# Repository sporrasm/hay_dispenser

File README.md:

Readme for project horse_feeder

Remeber to run the export script from ESP install dir!

To configure (once per project), run

```
idf.py set-target esp32
idf.py menuconfig
```
Alternatively, WiFi SSID and password can be
set with `wifi_config.sh`. Place SSID and password
in `wifi_info.txt` in the following format:

```
SSID=YOUR_NETWORK_SSID
PASS=YOUR_PASSWORD
```
`wifi_info.txt` is automatically ignored in version
control and thus your password is safe.

To build, run
```
idf.py build
```
Finally, to flash and monitor, run

```
idf.py -p ESP_SERIAL_PORT flash monitor
```

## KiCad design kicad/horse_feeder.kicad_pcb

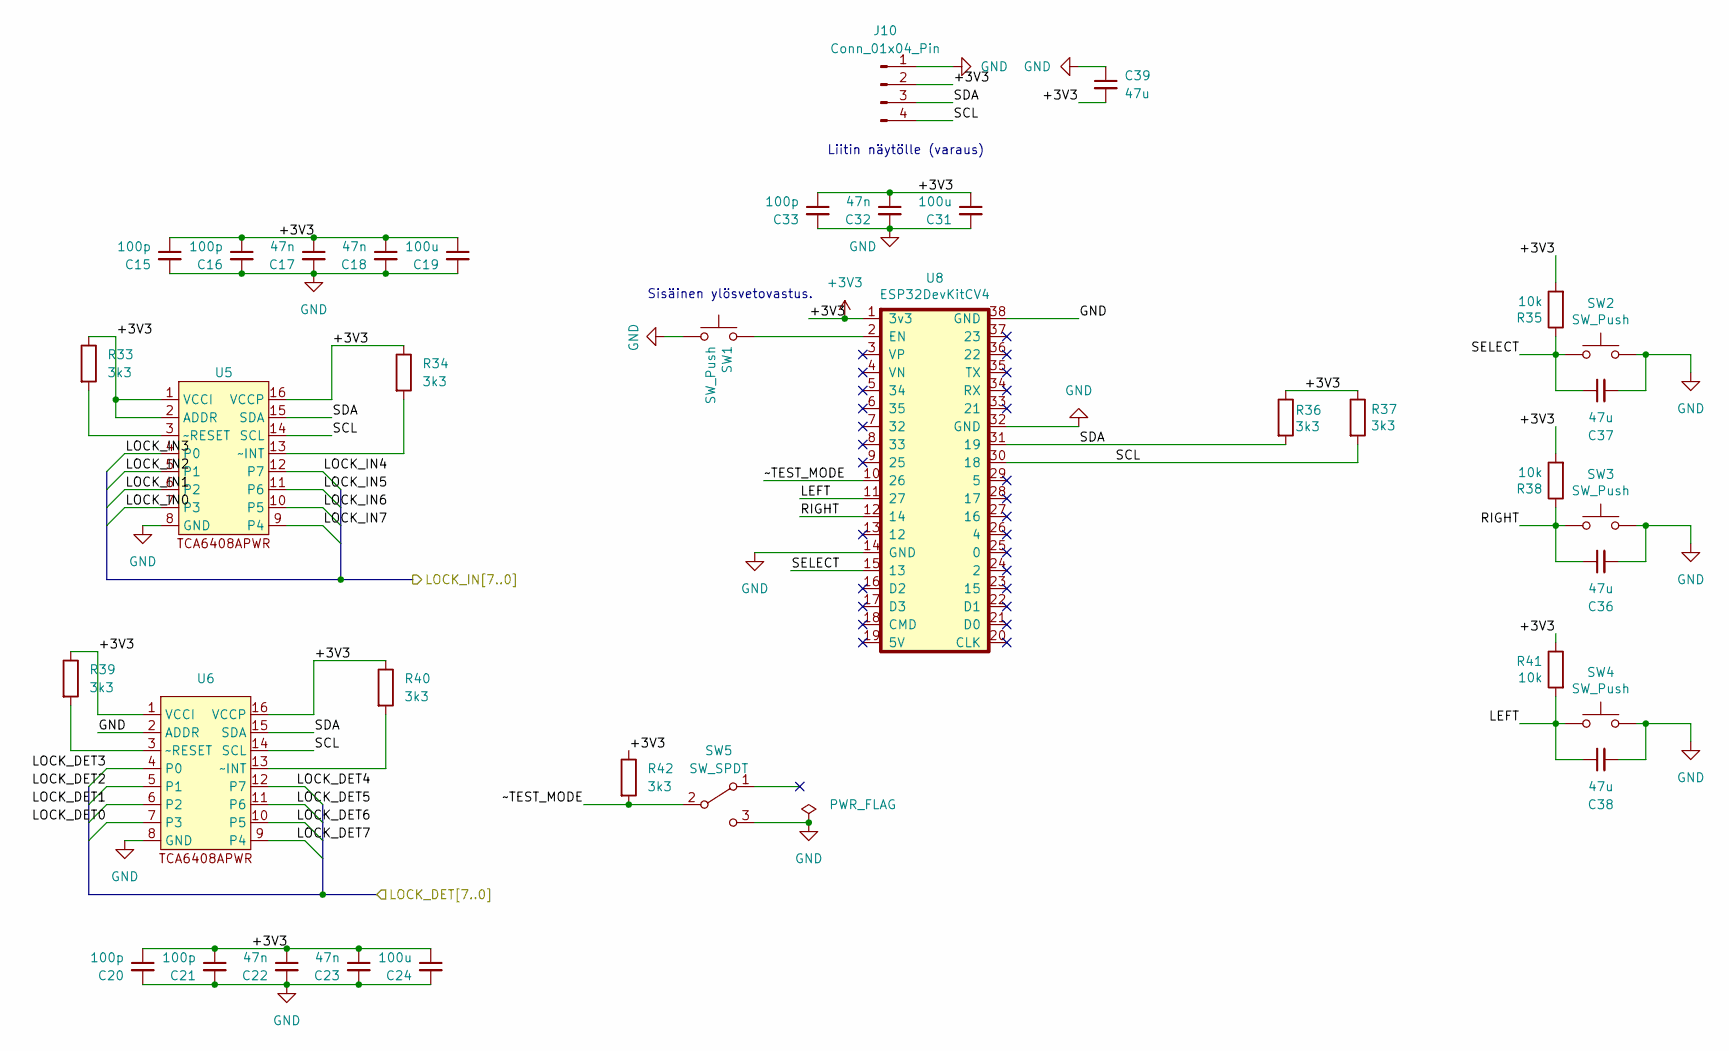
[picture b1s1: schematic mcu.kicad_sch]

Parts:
C15, C16, C20, C21, C33: 100p; C_0805_2012Metric_Pad1.18x1.45mm_HandSolder
C17, C18, C22, C23, C32: 47n; C_0805_2012Metric_Pad1.18x1.45mm_HandSolder
C19, C24, C31: 100u; CP_Radial_D5.0mm_P2.50mm
C36, C37, C38, C39: 47u; C_0805_2012Metric_Pad1.18x1.45mm_HandSolder
J10: Conn_01x04_Pin; PinHeader_1x04_P2.00mm_Vertical
R33, R34, R36, R37, R39, R40, R42: 3k3; R_0805_2012Metric_Pad1.20x1.40mm_HandSolder
R35, R38, R41: 10k; R_0805_2012Metric_Pad1.20x1.40mm_HandSolder
SW1, SW2, SW3, SW4: SW_Push; PinHeader_1x02_P2.54mm_Vertical
SW5: SW_SPDT; TE_826576-3_1x03_P3.96mm_Vertical
U5, U6: TSSOP-16_4.4x5mm_P0.65mm
U8: ESP32DevKitCV4; ESP32-DevkitC

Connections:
+3V3: C15.1, C16.1, C17.1, C18.1, C19.1, C20.1, C21.1, C22.1, C23.1, C24.1, C31.1, C32.1, C33.1, C39.2, J10.2, R33.1, R34.1, R35.2, R36.1, R37.1, R38.2, R39.1, R40.1, R41.1, R42.1, U5.1 (VCCI), U5.2 (ADDR), U5.16 (VCCP), U6.1 (VCCI), U6.16 (VCCP), U8.1 (3v3); also elsewhere on the board
/IOS/LOCK_DET0: U6.7 (P3); also elsewhere on the board
/IOS/LOCK_DET1: U6.6 (P2); also elsewhere on the board
/IOS/LOCK_DET2: U6.5 (P1); also elsewhere on the board
/IOS/LOCK_DET3: U6.4 (P0); also elsewhere on the board
/IOS/LOCK_DET4: U6.12 (P7); also elsewhere on the board
/IOS/LOCK_DET5: U6.11 (P6); also elsewhere on the board
/IOS/LOCK_DET6: U6.10 (P5); also elsewhere on the board
/IOS/LOCK_DET7: U6.9 (P4); also elsewhere on the board
/IOS/LOCK_IN0: U5.7 (P3); also elsewhere on the board
/IOS/LOCK_IN1: U5.6 (P2); also elsewhere on the board
/IOS/LOCK_IN2: U5.5 (P1); also elsewhere on the board
/IOS/LOCK_IN3: U5.4 (P0); also elsewhere on the board
/IOS/LOCK_IN4: U5.12 (P7); also elsewhere on the board
/IOS/LOCK_IN5: U5.11 (P6); also elsewhere on the board
/IOS/LOCK_IN6: U5.10 (P5); also elsewhere on the board
/IOS/LOCK_IN7: U5.9 (P4); also elsewhere on the board
/MCU/LEFT: C38.1, R41.2, SW4.2, U8.11 (27)
/MCU/RIGHT: C36.1, R38.1, SW3.2, U8.12 (14)
/MCU/SCL: J10.4, R37.2, U5.14 (SCL), U6.14 (SCL), U8.30 (18)
/MCU/SDA: J10.3, R36.2, U5.15 (SDA), U6.15 (SDA), U8.31 (19)
/MCU/SELECT: C37.1, R35.1, SW2.2, U8.15 (13)
/MCU/~TEST_MODE: R42.2, SW5.2 (B), U8.10 (26)
GND: C15.2, C16.2, C17.2, C18.2, C19.2, C20.2, C21.2, C22.2, C23.2, C24.2, C31.2, C32.2, C33.2, C36.2, C37.2, C38.2, C39.1, J10.1, SW1.1, SW2.1, SW3.1, SW4.1, SW5.3 (C), U5.8 (GND), U6.2 (ADDR), U6.8 (GND), U8.14 (GND), U8.32 (GND), U8.38 (GND); also elsewhere on the board
unnamed: R34.2, U5.13 (~INT)
unnamed: R33.2, U5.3 (~RESET)
unnamed: R40.2, U6.13 (~INT)
unnamed: R39.2, U6.3 (~RESET)
unnamed: SW1.2, U8.2 (EN)

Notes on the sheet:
Sisäinen ylösvetovastus.
Liitin näytölle (varaus)

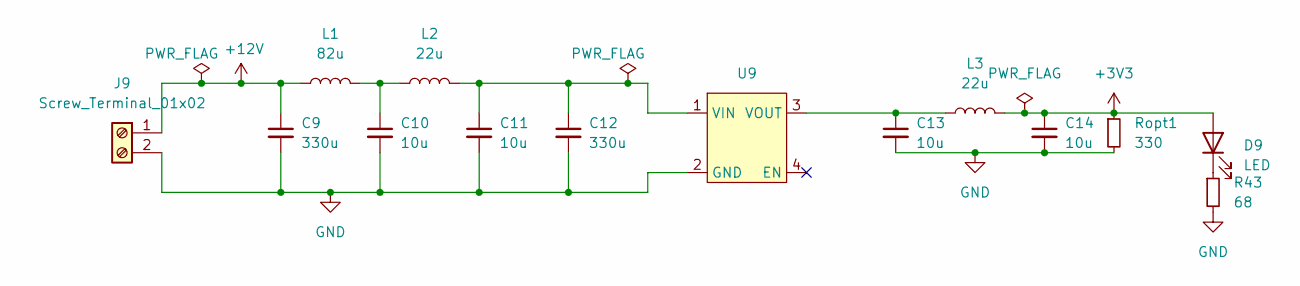
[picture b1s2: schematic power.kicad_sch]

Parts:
C9, C12: 330u; CP_Radial_D8.0mm_P3.50mm
C10, C11, C13, C14: 10u; CP_Radial_D5.0mm_P2.50mm
D9: LED; LED_PLCC-2_3x2mm_KA
J9: Screw_Terminal_01x02; PhoenixContact_MSTBA_2,5_2-G_1x02_P5.00mm_Horizontal
L1: 82u; L_Radial_D7.0mm_P3.00mm
L2, L3: 22u; L_Radial_D7.0mm_P3.00mm
R43: 68; R_0805_2012Metric_Pad1.20x1.40mm_HandSolder
Ropt1: 330; R_0805_2012Metric_Pad1.20x1.40mm_HandSolder
U9: AMSROL-783

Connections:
+3V3: C14.1, D9.2 (A), L3.2, Ropt1.1; also elsewhere on the board
+12V: C9.1, J9.1, L1.1; also elsewhere on the board
GND: C9.2, C10.2, C11.2, C12.2, C13.2, C14.2, J9.2, R43.2, Ropt1.2, U9.2 (GND); also elsewhere on the board
unnamed: C10.1, L1.2, L2.1
unnamed 50: D9.1 (K), R43.1; also elsewhere on the board
unnamed: C11.1, C12.1, L2.2, U9.1 (VIN)
unnamed: C13.1, L3.1, U9.3 (VOUT)

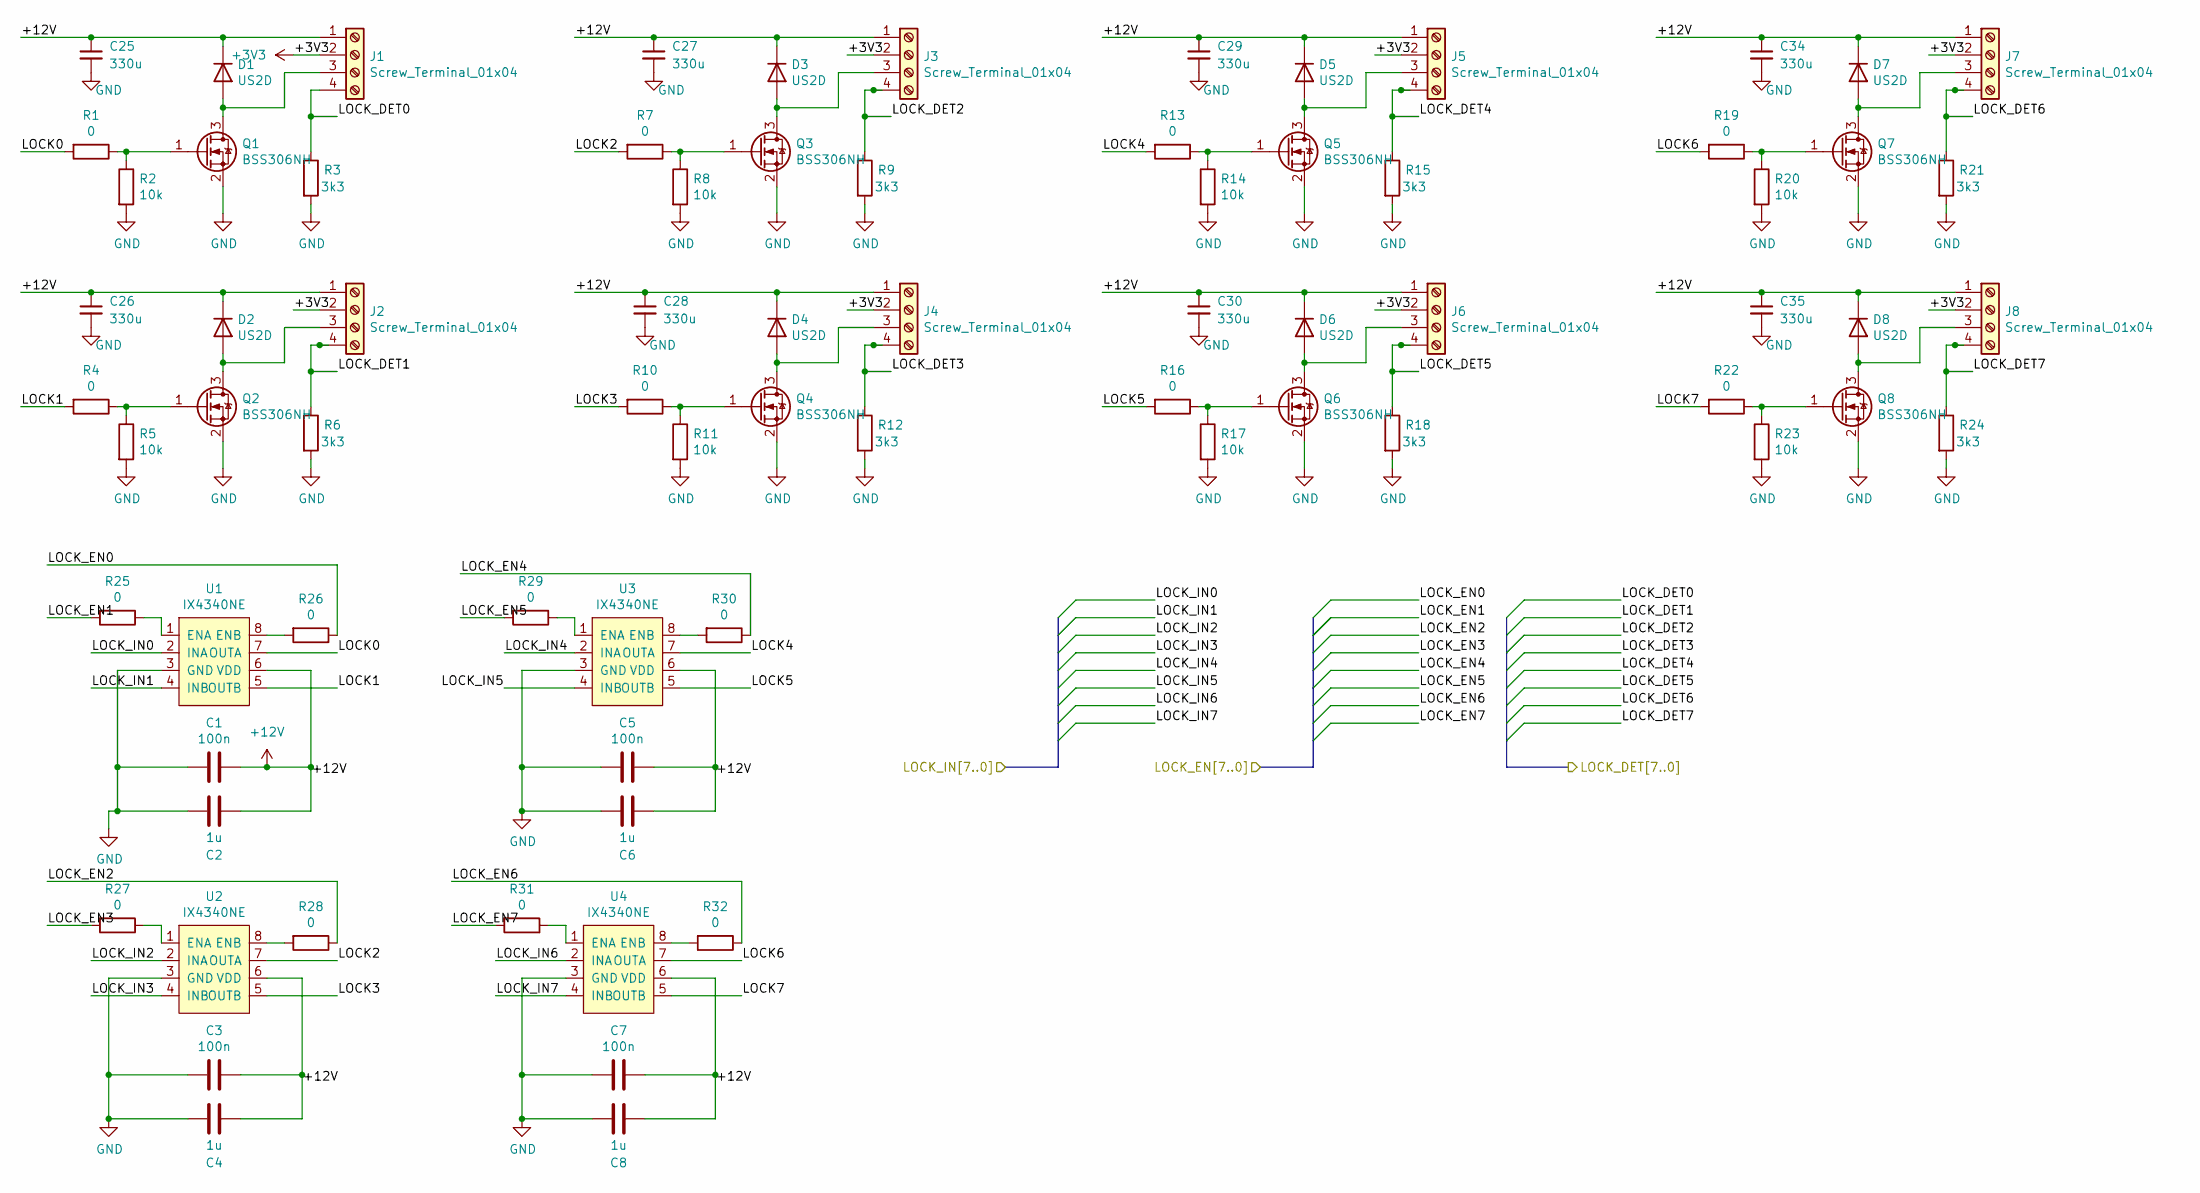
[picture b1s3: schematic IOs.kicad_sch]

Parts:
C1, C3, C5, C7: 100n; C_0805_2012Metric_Pad1.18x1.45mm_HandSolder
C2, C4, C6, C8: 1u; C_0805_2012Metric_Pad1.18x1.45mm_HandSolder
C25, C26, C27, C28, C29, C30, C34, C35: 330u; CP_Radial_D8.0mm_P3.50mm
D1, D2, D3, D4, D5, D6, D7, D8: US2D; D_SMB
J1, J2, J3, J4, J5, J6, J7, J8: Screw_Terminal_01x04; PinHeader_2x02_P2.54mm_Vertical
Q1, Q2, Q3, Q4, Q5, Q6, Q7, Q8: BSS306NH; SOT-23
R1, R4, R7, R10, R13, R16, R19, R22, R25, R26, R27, R28, R29, R30, R31, R32: 0; R_0805_2012Metric_Pad1.20x1.40mm_HandSolder
R2, R5, R8, R11, R14, R17, R20, R23: 10k; R_0805_2012Metric_Pad1.20x1.40mm_HandSolder
R3, R6, R9, R12, R15, R18, R21, R24: 3k3; R_0805_2012Metric_Pad1.20x1.40mm_HandSolder
U1, U2, U3, U4: IX4340NE; SOIC-8-1EP_3.9x4.9mm_P1.27mm_EP2.29x3mm

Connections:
+3V3: J1.2, J2.2, J3.2, J4.2, J5.2, J6.2, J7.2, J8.2; also elsewhere on the board
+12V: C1.1, C2.1, C3.1, C4.1, C5.1, C6.1, C7.1, C8.1, C25.1, C26.1, C27.1, C28.1, C29.1, C30.1, C34.1, C35.1, D1.1 (K), D2.1 (K), D3.1 (K), D4.1 (K), D5.1 (K), D6.1 (K), D7.1 (K), D8.1 (K), J1.1, J2.1, J3.1, J4.1, J5.1, J6.1, J7.1, J8.1, U1.6 (VDD), U2.6 (VDD), U3.6 (VDD), U4.6 (VDD); also elsewhere on the board
/IOS/LOCK0: R1.2, U1.7 (OUTA)
/IOS/LOCK1: R4.2, U1.5 (OUTB)
/IOS/LOCK2: R7.2, U2.7 (OUTA)
/IOS/LOCK3: R10.2, U2.5 (OUTB)
/IOS/LOCK4: R13.2, U3.7 (OUTA)
/IOS/LOCK5: R16.2, U3.5 (OUTB)
/IOS/LOCK6: R19.2, U4.7 (OUTA)
/IOS/LOCK7: R22.2, U4.5 (OUTB)
/IOS/LOCK_DET0: J1.4, R3.1; also elsewhere on the board
/IOS/LOCK_DET1: J2.4, R6.1; also elsewhere on the board
/IOS/LOCK_DET2: J3.4, R9.1; also elsewhere on the board
/IOS/LOCK_DET3: J4.4, R12.1; also elsewhere on the board
/IOS/LOCK_DET4: J5.4, R15.1; also elsewhere on the board
/IOS/LOCK_DET5: J6.4, R18.1; also elsewhere on the board
/IOS/LOCK_DET6: J7.4, R21.1; also elsewhere on the board
/IOS/LOCK_DET7: J8.4, R24.1; also elsewhere on the board
/IOS/LOCK_EN0: R26.1
/IOS/LOCK_EN1: R25.2
/IOS/LOCK_EN2: R28.1
/IOS/LOCK_EN3: R27.2
/IOS/LOCK_EN4: R30.1
/IOS/LOCK_EN5: R29.2
/IOS/LOCK_EN6: R32.1
/IOS/LOCK_EN7: R31.2
/IOS/LOCK_IN0: U1.2 (INA); also elsewhere on the board
/IOS/LOCK_IN1: U1.4 (INB); also elsewhere on the board
/IOS/LOCK_IN2: U2.2 (INA); also elsewhere on the board
/IOS/LOCK_IN3: U2.4 (INB); also elsewhere on the board
/IOS/LOCK_IN4: U3.2 (INA); also elsewhere on the board
/IOS/LOCK_IN5: U3.4 (INB); also elsewhere on the board
/IOS/LOCK_IN6: U4.2 (INA); also elsewhere on the board
/IOS/LOCK_IN7: U4.4 (INB); also elsewhere on the board
GND: C1.2, C2.2, C3.2, C4.2, C5.2, C6.2, C7.2, C8.2, C25.2, C26.2, C27.2, C28.2, C29.2, C30.2, C34.2, C35.2, Q1.2 (S), Q2.2 (S), Q3.2 (S), Q4.2 (S), Q5.2 (S), Q6.2 (S), Q7.2 (S), Q8.2 (S), R2.2, R3.2, R5.2, R6.2, R8.2, R9.2, R11.2, R12.2, R14.2, R15.2, R17.2, R18.2, R20.2, R21.2, R23.2, R24.2, U1.3 (GND), U2.3 (GND), U3.3 (GND), U4.3 (GND); also elsewhere on the board
unnamed: D1.2 (A), J1.3, Q1.3 (D)
unnamed: D2.2 (A), J2.3, Q2.3 (D)
unnamed: D3.2 (A), J3.3, Q3.3 (D)
unnamed: D4.2 (A), J4.3, Q4.3 (D)
unnamed: D5.2 (A), J5.3, Q5.3 (D)
unnamed: D6.2 (A), J6.3, Q6.3 (D)
unnamed: D7.2 (A), J7.3, Q7.3 (D)
unnamed: D8.2 (A), J8.3, Q8.3 (D)
unnamed: Q1.1 (G), R1.1, R2.1
unnamed: Q2.1 (G), R4.1, R5.1
unnamed: Q3.1 (G), R7.1, R8.1
unnamed: Q4.1 (G), R10.1, R11.1
unnamed: Q5.1 (G), R13.1, R14.1
unnamed: Q6.1 (G), R16.1, R17.1
unnamed: Q7.1 (G), R19.1, R20.1
unnamed: Q8.1 (G), R22.1, R23.1
unnamed: R25.1, U1.1 (ENA)
unnamed: R26.2, U1.8 (ENB)
unnamed: R27.1, U2.1 (ENA)
unnamed: R28.2, U2.8 (ENB)
unnamed: R29.1, U3.1 (ENA)
unnamed: R30.2, U3.8 (ENB)
unnamed: R31.1, U4.1 (ENA)
unnamed: R32.2, U4.8 (ENB)

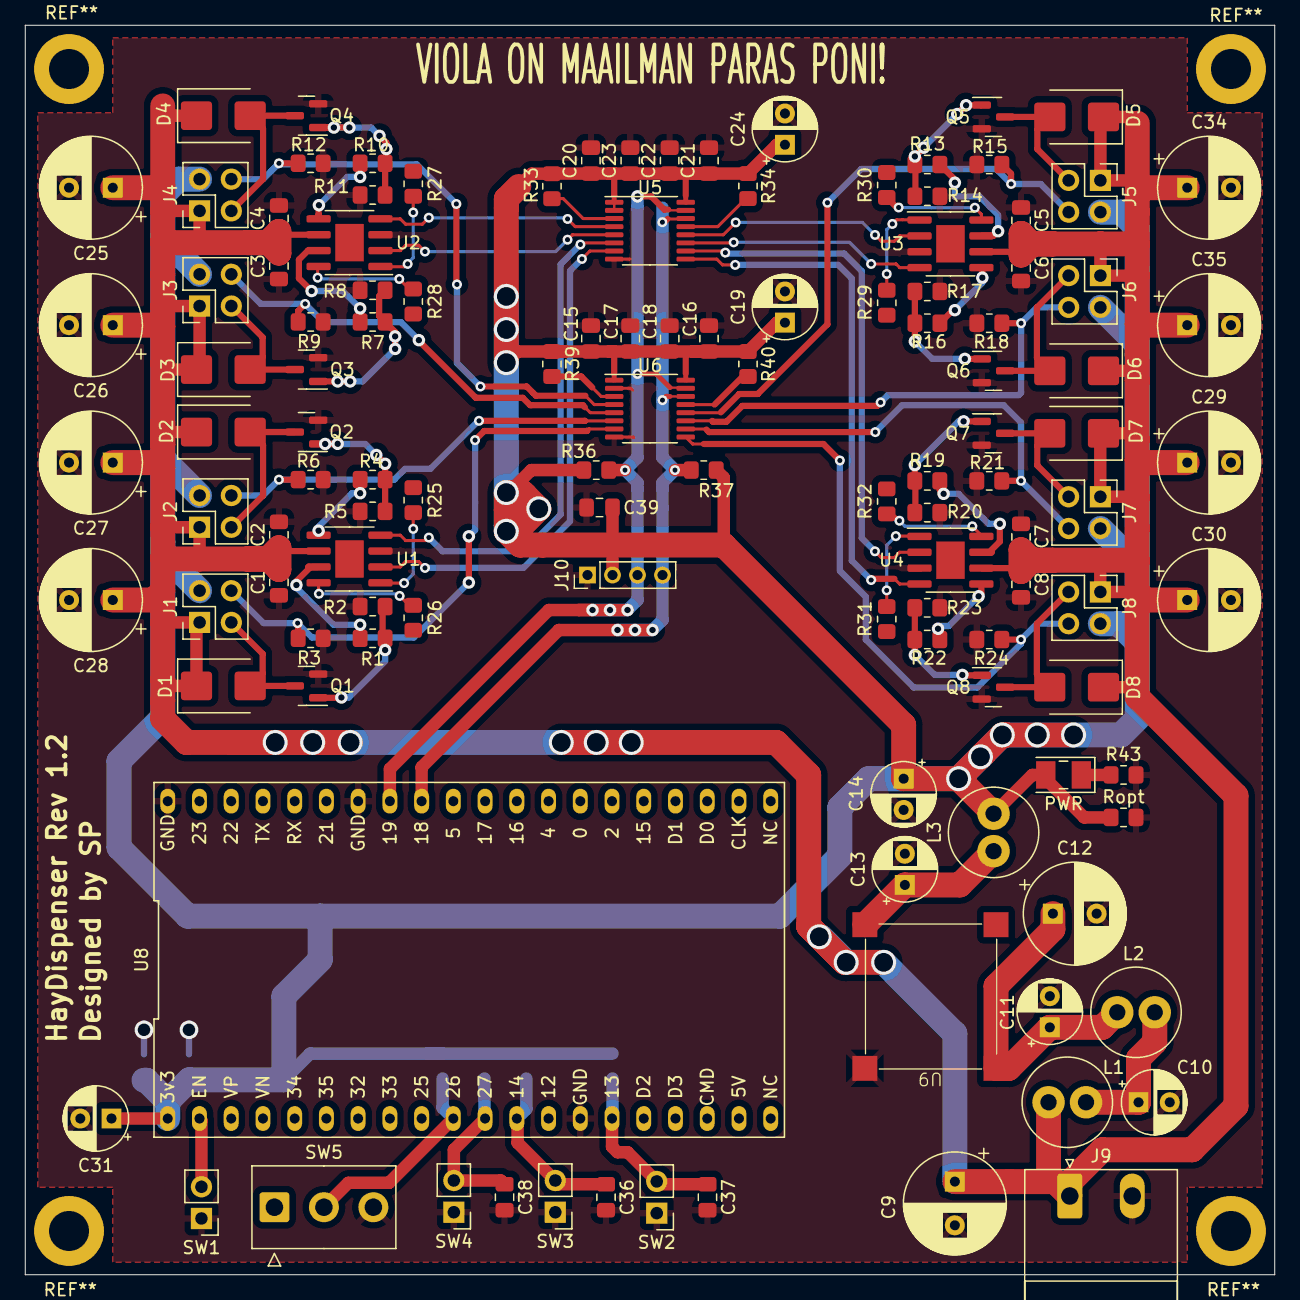
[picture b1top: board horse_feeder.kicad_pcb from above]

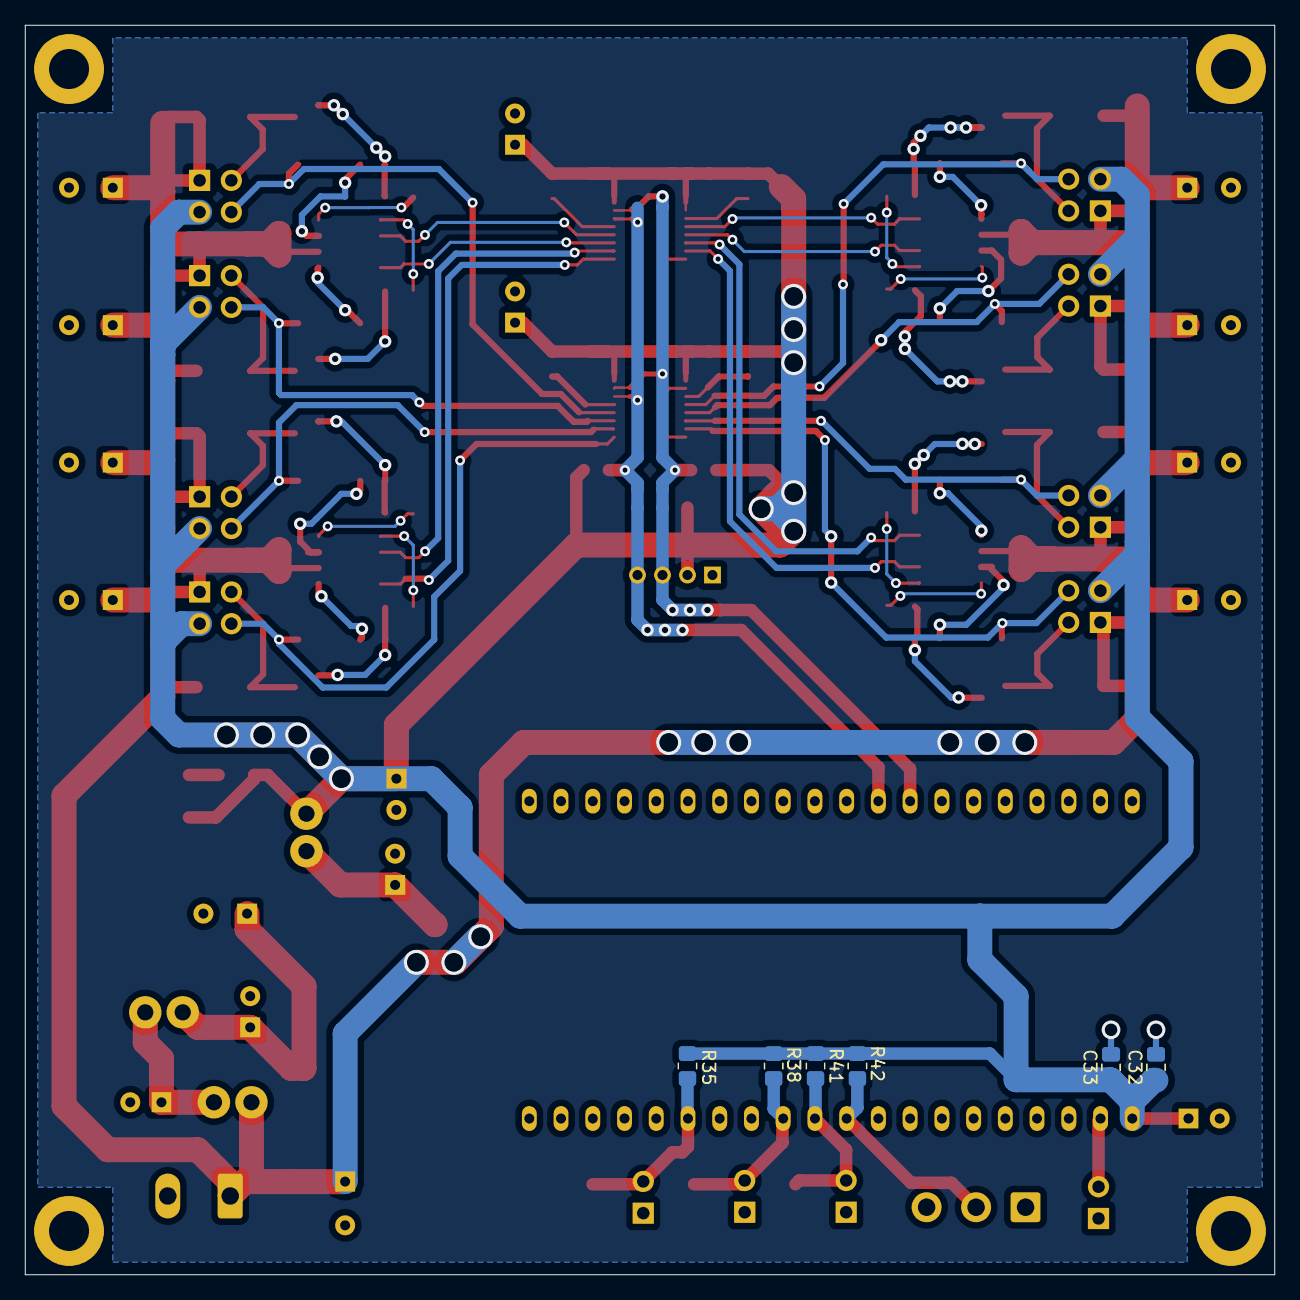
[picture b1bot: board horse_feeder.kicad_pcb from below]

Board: 2 copper layers, 100.0 x 100.0 mm, 126 parts (6 on the bottom side), 66 nets.

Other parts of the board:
PWR: LED; LED_PLCC-2_3x2mm_KA
Ropt: 330; R_0805_2012Metric_Pad1.20x1.40mm_HandSolder

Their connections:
+3V3: PWR.2 (A), Ropt.1; also elsewhere on the board
GND: Ropt.2; also elsewhere on the board
unnamed 50: PWR.1 (K); also elsewhere on the board

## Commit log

2021-09-08 WiFi connection works
2021-09-11 get_time works
2021-09-11 Setting system time works
2021-09-12 Add primitive library for Grove 16x02 LCD
2021-09-12 Add datasheet(s) for LCD
2021-09-12 Printing local time to LCD works
2021-09-12 Update instruction for configuring wifi
2021-09-12 Add schematic
2021-09-13 Time string to local time conversion works
2021-09-14 Fix bug with localtime()
2021-09-14 Fix erratic behaviour with LCD time
2021-09-15 Improvements to LCD_update
2021-09-17 Timer works
2021-09-20 Moved timer related stuff to own file
2021-09-20 Timer retriggering works poorly
2021-09-23 Timer works, need to reshuffle times after final value
2021-09-24 Ideas for recovering lock_idx
2021-09-25 Renamed timer to timer_handler
2021-09-25 Add gpio_funcs (WIP)
2021-09-25 GPIO power down interrupt works
2021-09-25 Update schematic
2021-09-25 Fix timer alarm value input
2021-09-26 Cast alarm values to uint64_t in update task as well
2021-09-26 Add idea for controlling the LCD screen
2021-10-02 Switch debouncing in software works
2021-10-02 Got rid of redundant task parameter
2021-10-03 Improved handling of left/right buttons
2021-10-03 Try to build user interface
2021-10-09 UI is a bit wonky
2021-10-09 Better approach, still needs some work though...
2021-10-12 Ready for outdoor test
2022-01-16 Modified schematic and PCB
2022-01-16 Added pullups for I2C
2022-02-19 Add testmode
2022-02-20 Fix for hardware
2022-02-20 Test with produced PCB
2022-02-26 Changed configuration
2022-02-26 Updated code to reflect different configurations
2022-03-12 Adjust logging levels
2023-03-18 KiCAD latest version now up to date
2023-03-18 esp-wifi-logger as submodule
2023-03-18 Latest update to program
2023-07-03 Update PCB with IO expander
2023-07-04 Fix remaining DRC + ERC, ready for manufacturing
2023-07-04 PCB order
2023-09-04 Timer works with latest software
2023-09-17 Deleted AIP31068L repo before adding it as submodule
2023-09-17 Add AIP31068L as a submodule
2023-09-17 GPIO control to IO expander
2023-09-18 Remove gpio funcs + timer works
2023-09-18 Timer updates
2023-09-18 Move source files to src
2023-09-18 Add misc. pdffiles
2023-09-18 Ignore kicad lock files
2023-09-18 Add missing component
2023-10-03 Add lock cover 3d model
2023-10-03 Add 3d model as STL file
2023-10-05 Update 3d model
2023-10-05 Slight modifications based on print results
2023-10-29 Add flag for i2c already inited when initing LCD
2023-10-29 Fix test mode offset calculation
